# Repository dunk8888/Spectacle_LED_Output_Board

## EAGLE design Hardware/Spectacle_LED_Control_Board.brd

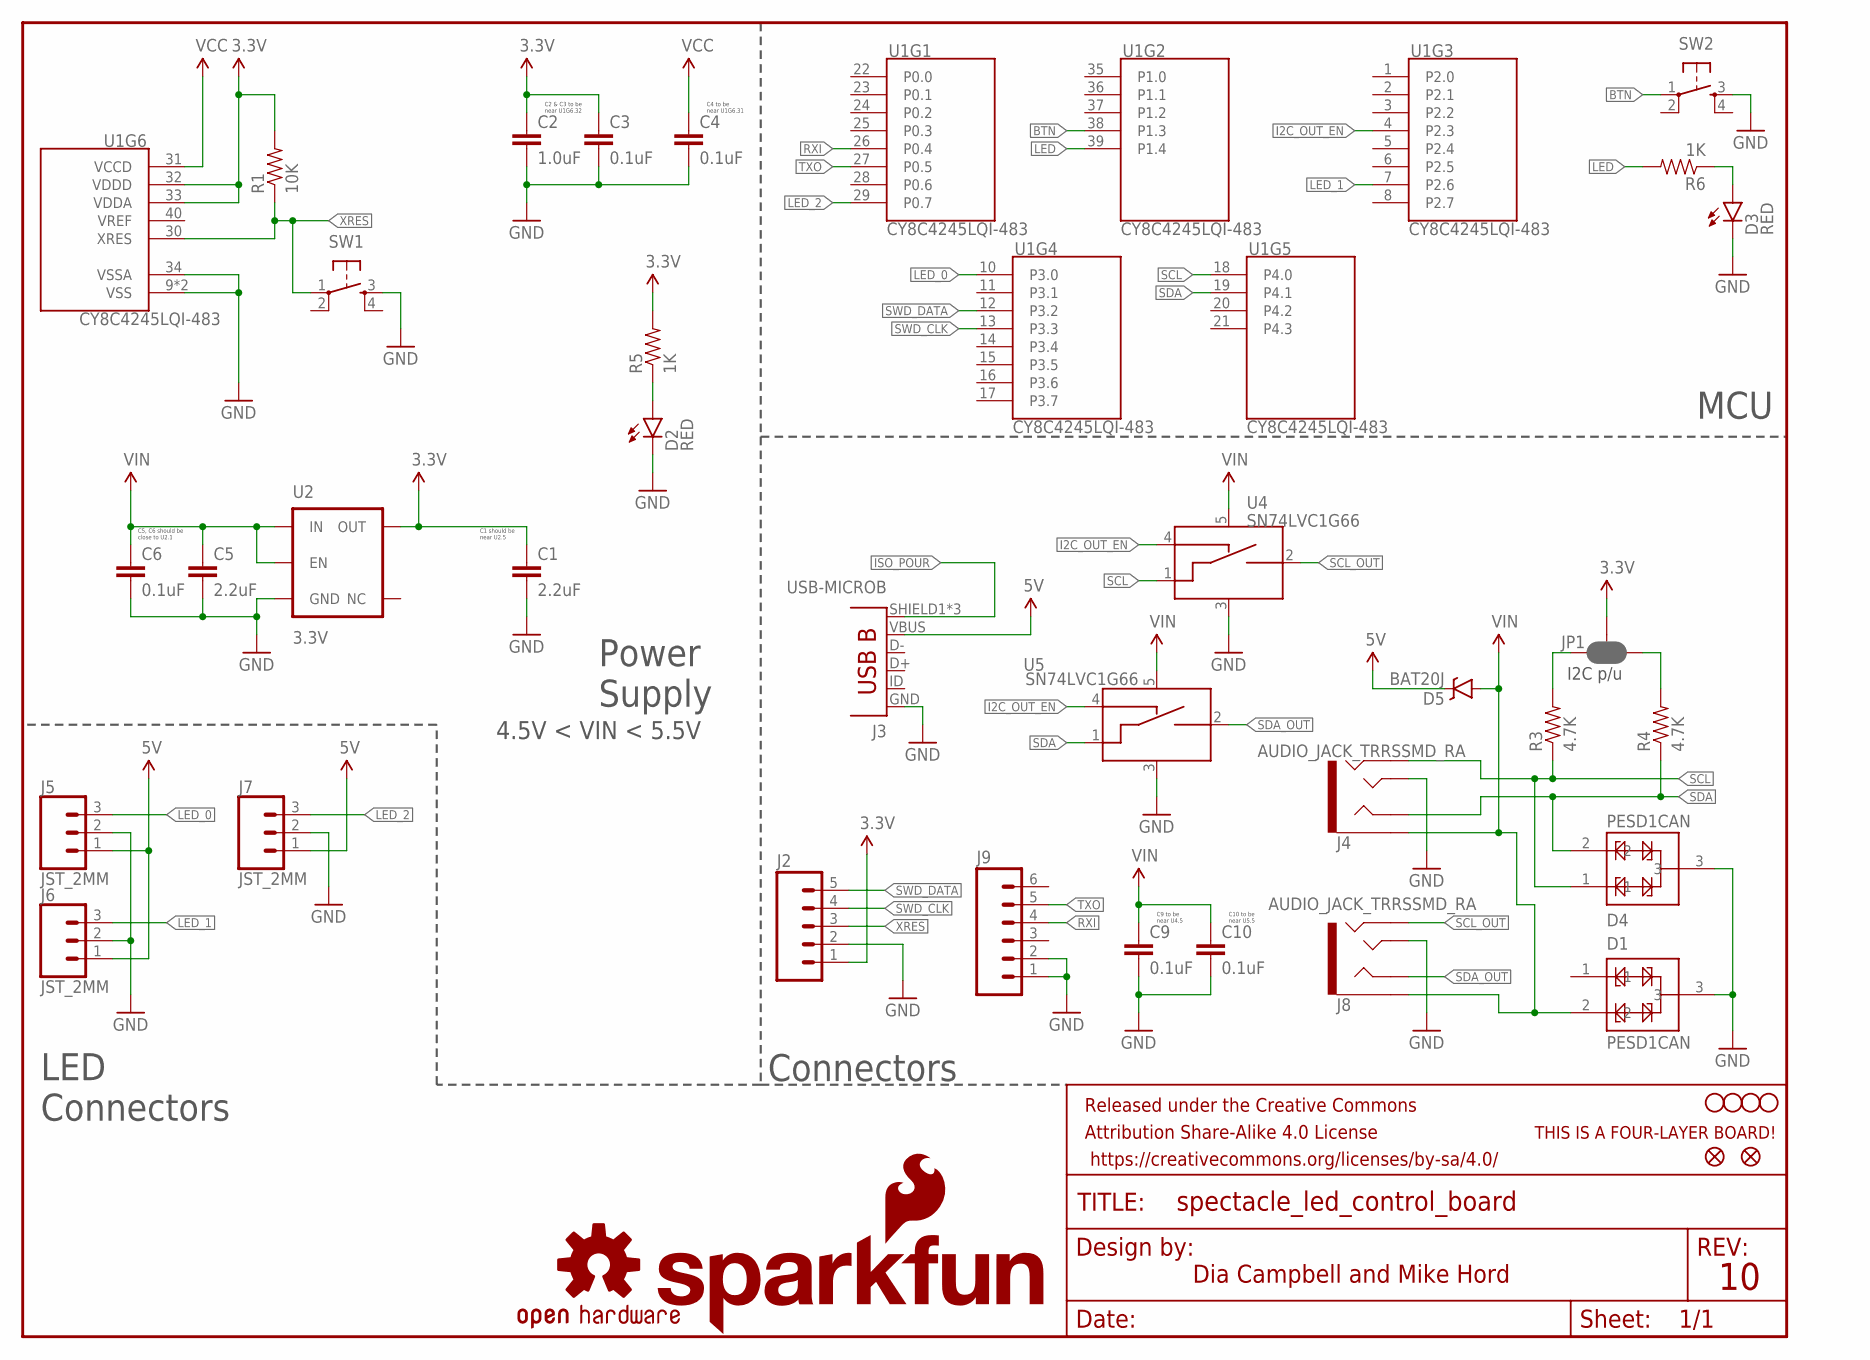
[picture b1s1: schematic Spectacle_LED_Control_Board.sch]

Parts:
C1, C5: 2.2uF; 0603-CAP
C2: 1.0uF; 0402-CAP
C3, C4, C6, C9, C10: 0.1uF; 0402-CAP
D1, D4: PESD1CAN; SOT23-3
D2, D3: RED; LED-0603
D5: BAT20J; SOD-323
FD1, FD2: FIDUCIALUFIDUCIAL; MICRO-FIDUCIAL
FRAME1: FRAME-LETTER; CREATIVE_COMMONS
H1, H2, H3, H4: STAND-OFF
J2: M05NO_SILK; 1X05_NO_SILK
J3: USB-MICROB; USB-B-MICRO-SMD_V03
J4, J8: AUDIO_JACK_TRRSSMD_RA; AUDIO_JACK_3.5MM_TRRS_SMD_RA
J5, J6, J7: JST_2MM; JST-3-PTH-VERT
J9: M06NO_SILK_NO_POP; 1X06_NO_SILK
JP1: JUMPER-PAD-3-NC_BY_PASTE; PAD-JUMPER-3-NC_BY_PASTE_YES_SILK_FULL_BOX
LOGO1: OSHW-LOGOS; OSHW-LOGO-S
LOGO2: SFE_LOGO_NAME_FLAME.1_INCH; SFE_LOGO_NAME_FLAME_.1
R1: 10K; 0603-RES
R3, R4: 4.7K; 0603-RES
R5, R6: 1K; 0603-RES
SW1, SW2: SWITCH_SPST_4_PINRECT; TACTILE_SWITCH_SMD_4.6X2.8MM
U1: CY8C4245LQI-483; QFN-40
U2: 3.3V; SOT23-5
U4, U5: SN74LVC1G66; SOT23-5
U$1: FOUR_LAYER_WARNING

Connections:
3.3V: C1.1, C2.1, C3.1, J2.1, JP1.2, R1.2, R5.2, U1.32 (VDDD), U1.33 (VDDA), U2.5 (OUT)
5V: D5.C, J3.VBUS, J5.1, J6.1, J7.1
BTN: SW2.1, U1.38 (P1.3)
GND: C1.2, C2.2, C3.2, C4.2, C5.2, C6.2, C9.2, C10.2, D1.3, D2.C, D3.C, D4.3, J2.2, J3.GND, J4.TIP, J5.2, J6.2, J7.2, J8.TIP, J9.1, J9.2, SW1.3, SW2.3, U1.9 (VSS), U1.34 (VSSA), U1.EP (VSS), U2.2 (GND), U4.3 (VSS), U5.3 (VSS)
I2C_OUT_EN: U1.4 (P2.3), U4.4 (CTRL_IN), U5.4 (CTRL_IN)
ISO_POUR: J3.SHIELD1 (SHIELD), J3.SHIELD2 (SHIELD), J3.SHIELD3 (SHIELD)
LED: R6.2, U1.39 (P1.4)
LED_0: J5.3, U1.10 (P3.0)
LED_1: J6.3, U1.7 (P2.6)
LED_2: J7.3, U1.29 (P0.7)
unnamed: JP1.3, R3.2
unnamed: D2.A, R5.1
unnamed: D3.A, R6.1
unnamed: JP1.1, R4.2
RXI: J9.4, U1.26 (P0.4)
SCL: D4.1, J4.RING2, R3.1, U1.18 (P4.0), U4.1 (A_IN)
SCL_OUT: J8.RING2, U4.2 (A_OUT)
SDA: D4.2, J4.RING1, R4.1, U1.19 (P4.1), U5.1 (A_IN)
SDA_OUT: J8.RING1, U5.2 (A_OUT)
SWD_CLK: J2.4, U1.13 (P3.3)
SWD_DATA: J2.5, U1.12 (P3.2)
TXO: J9.5, U1.27 (P0.5)
VCC: C4.1, U1.31 (VCCD)
VIN: C5.1, C6.1, C9.1, C10.1, D1.2, D5.A, J4.EARTH, J8.EARTH, U2.1 (IN), U2.3 (EN), U4.5 (VCC), U5.5 (VCC)
XRES: J2.3, R1.1, SW1.1, U1.30 (XRES)

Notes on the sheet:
C2 & C3 to be near U1G6.32
C4 to be near U1G6.31
Dia Campbell and Mike Hord
MCU
Connectors
LED Connectors
Power Supply
4.5V < VIN < 5.5V
I2C p/u
C9 to be near U4.5
C10 to be near U5.5
C5, C6 should be close to U2.1
C1 should be near U2.5

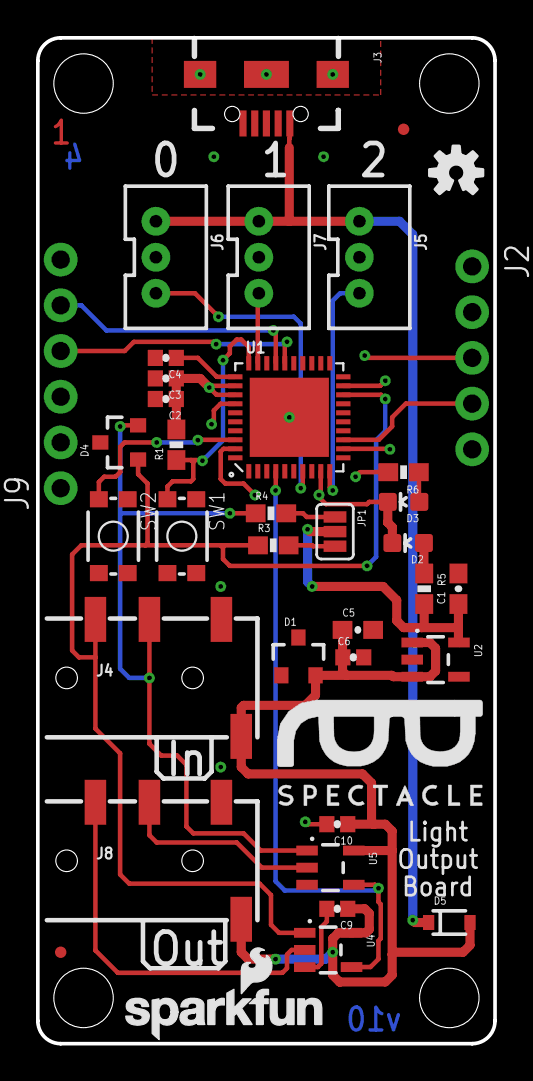
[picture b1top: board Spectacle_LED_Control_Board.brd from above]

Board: 4 copper layers, 25.4 x 55.9 mm, 44 parts (0 on the bottom side), 25 nets.

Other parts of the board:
U$2: ORDERING_INSTRUCTIONS

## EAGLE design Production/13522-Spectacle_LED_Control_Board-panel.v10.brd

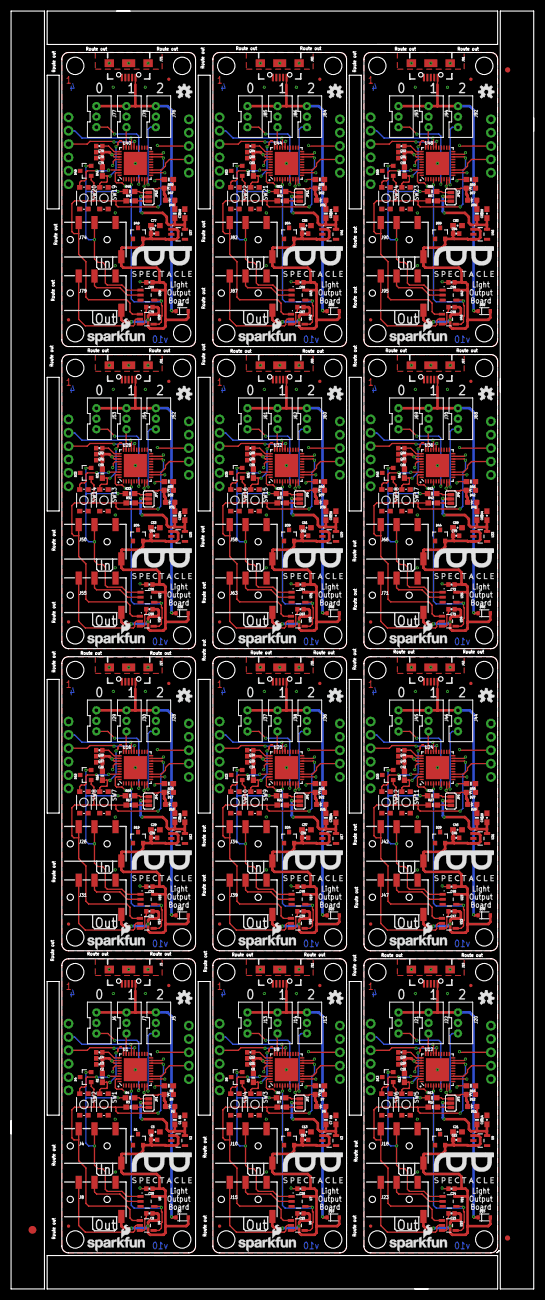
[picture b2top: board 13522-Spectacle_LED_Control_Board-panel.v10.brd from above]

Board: 4 copper layers, 99.3 x 242.8 mm, 495 parts (0 on the bottom side), 300 nets.

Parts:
C1, C5, C7, C13, C17, C21, C25, C29, C33, C37, C41, C45, C49, C53, C57, C61, C65, C69, C73, C77, C81, C85, C89, C93: 2.2uF; 0603-CAP
C2, C8, C18, C26, C34, C42, C50, C58, C66, C74, C82, C90: 1.0uF; 0402-CAP
C3, C4, C6, C9, C10, C11, C12, C14, C15, C16, C19, C20, C22, C23, C24, C27, C28, C30, C31, C32, C35, C36, C38, C39, C40, C43, C44, C46, C47, C48, C51, C52, C54, C55, C56, C59, C60, C62, C63, C64, C67, C68, C70, C71, C72, C75, C76, C78, C79, C80, C83, C84, C86, C87, C88, C91, C92, C94, C95, C96: 0.1uF; 0402-CAP
D1, D4, D8, D9, D13, D14, D18, D19, D23, D24, D28, D29, D33, D34, D38, D39, D43, D44, D48, D49, D53, D54, D58, D59: PESD1CAN; SOT23-3
D2, D3, D6, D7, D11, D12, D16, D17, D21, D22, D26, D27, D31, D32, D36, D37, D41, D42, D46, D47, D51, D52, D56, D57: RED; LED-0603
D5, D10, D15, D20, D25, D30, D35, D40, D45, D50, D55, D60: BAT20J; SOD-323
E$1: FIDUCIAL-1.5X3
E$4, E$7: FIDUCIAL-1X2
FD1, FD2, FD3, FD4, FD5, FD6, FD7, FD8, FD9, FD10, FD11, FD12, FD13, FD14, FD15, FD16, FD17, FD18, FD19, FD20, FD21, FD22, FD23, FD24: FIDUCIALUFIDUCIAL; MICRO-FIDUCIAL
H1, H2, H3, H4, H5, H6, H7, H8, H9, H10, H11, H12, H13, H14, H15, H16, H17, H18, H19, H20, H21, H22, H23, H24, H25, H26, H27, H28, H29, H30, H31, H32, H33, H34, H35, H36, H37, H38, H39, H40, H41, H42, H43, H44, H45, H46, H47, H48: STAND-OFF
J1, J2, J17, J25, J33, J41, J49, J57, J65, J73, J81, J89: 1X05_NO_SILK
J3, J11, J19, J27, J35, J43, J51, J59, J67, J75, J83, J91: USB-MICROB; USB-B-MICRO-SMD_V03
J4, J8, J10, J15, J18, J23, J26, J31, J34, J39, J42, J47, J50, J55, J58, J63, J66, J71, J74, J79, J82, J87, J90, J95: AUDIO_JACK_TRRSSMD_RA; AUDIO_JACK_3.5MM_TRRS_SMD_RA
J5, J6, J7, J12, J13, J14, J20, J21, J22, J28, J29, J30, J36, J37, J38, J44, J45, J46, J52, J53, J54, J60, J61, J62, J68, J69, J70, J76, J77, J78, J84, J85, J86, J92, J93, J94: JST_2MM; JST-3-PTH-VERT
J9, J16, J24, J32, J40, J48, J56, J64, J72, J80, J88, J96: 1X06_NO_SILK
JP1, JP2, JP3, JP4, JP5, JP6, JP7, JP8, JP9, JP10, JP11, JP12: JUMPER-PAD-3-NC_BY_PASTE; PAD-JUMPER-3-NC_BY_PASTE_YES_SILK_FULL_BOX
LOGO1, LOGO3, LOGO5, LOGO7, LOGO9, LOGO11, LOGO13, LOGO15, LOGO17, LOGO19, LOGO21, LOGO23: OSHW-LOGOS; OSHW-LOGO-S
LOGO2, LOGO4, LOGO6, LOGO8, LOGO10, LOGO12, LOGO14, LOGO16, LOGO18, LOGO20, LOGO22, LOGO24: SFE_LOGO_NAME_FLAME.1_INCH; SFE_LOGO_NAME_FLAME_.1
R1, R2, R11, R16, R21, R26, R31, R36, R41, R46, R51, R56: 10K; 0603-RES
R3, R4, R7, R8, R12, R13, R17, R18, R22, R23, R27, R28, R32, R33, R37, R38, R42, R43, R47, R48, R52, R53, R57, R58: 4.7K; 0603-RES
R5, R6, R9, R10, R14, R15, R19, R20, R24, R25, R29, R30, R34, R35, R39, R40, R44, R45, R49, R50, R54, R55, R59, R60: 1K; 0603-RES
SW1, SW2, SW3, SW4, SW5, SW6, SW7, SW8, SW9, SW10, SW11, SW12, SW13, SW14, SW15, SW16, SW17, SW18, SW19, SW20, SW21, SW22, SW23, SW24: TACTILE_SWITCH_SMD_4.6X2.8MM
U1, U8, U12, U16, U20, U24, U28, U32, U36, U40, U44, U48: CY8C4245LQI-483; QFN-40
U2, U3, U9, U13, U17, U21, U25, U29, U33, U37, U41, U45: 3.3V; SOT23-5
U4, U5, U6, U7, U10, U11, U14, U15, U18, U19, U22, U23, U26, U27, U30, U31, U34, U35, U38, U39, U42, U43, U46, U47: SN74LVC1G66; SOT23-5

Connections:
3.3V: C1.1, C2.1, C3.1, J2.1, JP1.2, R1.2, R5.2, U1.32, U1.33, U2.5
3.3V1: C7.1, C8.1, C11.1, J1.1, JP2.2, R2.2, R9.2, U3.5, U8.32, U8.33
3.3V2: C17.1, C18.1, C19.1, J17.1, JP3.2, R11.2, R14.2, U9.5, U12.32, U12.33
3.3V3: C25.1, C26.1, C27.1, J25.1, JP4.2, R16.2, R19.2, U13.5, U16.32, U16.33
3.3V4: C33.1, C34.1, C35.1, J33.1, JP5.2, R21.2, R24.2, U17.5, U20.32, U20.33
3.3V5: C41.1, C42.1, C43.1, J41.1, JP6.2, R26.2, R29.2, U21.5, U24.32, U24.33
3.3V6: C49.1, C50.1, C51.1, J49.1, JP7.2, R31.2, R34.2, U25.5, U28.32, U28.33
3.3V7: C57.1, C58.1, C59.1, J57.1, JP8.2, R36.2, R39.2, U29.5, U32.32, U32.33
3.3V8: C65.1, C66.1, C67.1, J65.1, JP9.2, R41.2, R44.2, U33.5, U36.32, U36.33
3.3V9: C73.1, C74.1, C75.1, J73.1, JP10.2, R46.2, R49.2, U37.5, U40.32, U40.33
3.3V10: C81.1, C82.1, C83.1, J81.1, JP11.2, R51.2, R54.2, U41.5, U44.32, U44.33
3.3V11: C89.1, C90.1, C91.1, J89.1, JP12.2, R56.2, R59.2, U45.5, U48.32, U48.33
5V: D5.C, J3.VBUS, J5.1, J6.1, J7.1
5V1: D10.C, J11.VBUS, J12.1, J13.1, J14.1
5V2: D15.C, J19.VBUS, J20.1, J21.1, J22.1
5V3: D20.C, J27.VBUS, J28.1, J29.1, J30.1
5V4: D25.C, J35.VBUS, J36.1, J37.1, J38.1
5V5: D30.C, J43.VBUS, J44.1, J45.1, J46.1
5V6: D35.C, J51.VBUS, J52.1, J53.1, J54.1
5V7: D40.C, J59.VBUS, J60.1, J61.1, J62.1
5V8: D45.C, J67.VBUS, J68.1, J69.1, J70.1
5V9: D50.C, J75.VBUS, J76.1, J77.1, J78.1
5V10: D55.C, J83.VBUS, J84.1, J85.1, J86.1
5V11: D60.C, J91.VBUS, J92.1, J93.1, J94.1
BTN: SW2.1, U1.38
BTN1: SW4.1, U8.38
BTN2: SW6.1, U12.38
BTN3: SW8.1, U16.38
BTN4: SW10.1, U20.38
BTN5: SW12.1, U24.38
BTN6: SW14.1, U28.38
BTN7: SW16.1, U32.38
BTN8: SW18.1, U36.38
BTN9: SW20.1, U40.38
BTN10: SW22.1, U44.38
BTN11: SW24.1, U48.38
GND: C1.2, C2.2, C3.2, C4.2, C5.2, C6.2, C9.2, C10.2, D1.3, D2.C, D3.C, D4.3, J2.2, J3.GND, J4.TIP, J5.2, J6.2, J7.2, J8.TIP, J9.1, J9.2, SW1.3, SW2.3, U1.9, U1.34, U1.EP, U2.2, U4.3, U5.3
GND1: C7.2, C8.2, C11.2, C12.2, C13.2, C14.2, C15.2, C16.2, D6.C, D7.C, D8.3, D9.3, J1.2, J10.TIP, J11.GND, J12.2, J13.2, J14.2, J15.TIP, J16.1, J16.2, SW3.3, SW4.3, U3.2, U6.3, U7.3, U8.9, U8.34, U8.EP
GND2: C17.2, C18.2, C19.2, C20.2, C21.2, C22.2, C23.2, C24.2, D11.C, D12.C, D13.3, D14.3, J17.2, J18.TIP, J19.GND, J20.2, J21.2, J22.2, J23.TIP, J24.1, J24.2, SW5.3, SW6.3, U9.2, U10.3, U11.3, U12.9, U12.34, U12.EP
GND3: C25.2, C26.2, C27.2, C28.2, C29.2, C30.2, C31.2, C32.2, D16.C, D17.C, D18.3, D19.3, J25.2, J26.TIP, J27.GND, J28.2, J29.2, J30.2, J31.TIP, J32.1, J32.2, SW7.3, SW8.3, U13.2, U14.3, U15.3, U16.9, U16.34, U16.EP
GND4: C33.2, C34.2, C35.2, C36.2, C37.2, C38.2, C39.2, C40.2, D21.C, D22.C, D23.3, D24.3, J33.2, J34.TIP, J35.GND, J36.2, J37.2, J38.2, J39.TIP, J40.1, J40.2, SW9.3, SW10.3, U17.2, U18.3, U19.3, U20.9, U20.34, U20.EP
GND5: C41.2, C42.2, C43.2, C44.2, C45.2, C46.2, C47.2, C48.2, D26.C, D27.C, D28.3, D29.3, J41.2, J42.TIP, J43.GND, J44.2, J45.2, J46.2, J47.TIP, J48.1, J48.2, SW11.3, SW12.3, U21.2, U22.3, U23.3, U24.9, U24.34, U24.EP
GND6: C49.2, C50.2, C51.2, C52.2, C53.2, C54.2, C55.2, C56.2, D31.C, D32.C, D33.3, D34.3, J49.2, J50.TIP, J51.GND, J52.2, J53.2, J54.2, J55.TIP, J56.1, J56.2, SW13.3, SW14.3, U25.2, U26.3, U27.3, U28.9, U28.34, U28.EP
GND7: C57.2, C58.2, C59.2, C60.2, C61.2, C62.2, C63.2, C64.2, D36.C, D37.C, D38.3, D39.3, J57.2, J58.TIP, J59.GND, J60.2, J61.2, J62.2, J63.TIP, J64.1, J64.2, SW15.3, SW16.3, U29.2, U30.3, U31.3, U32.9, U32.34, U32.EP
GND8: C65.2, C66.2, C67.2, C68.2, C69.2, C70.2, C71.2, C72.2, D41.C, D42.C, D43.3, D44.3, J65.2, J66.TIP, J67.GND, J68.2, J69.2, J70.2, J71.TIP, J72.1, J72.2, SW17.3, SW18.3, U33.2, U34.3, U35.3, U36.9, U36.34, U36.EP
GND9: C73.2, C74.2, C75.2, C76.2, C77.2, C78.2, C79.2, C80.2, D46.C, D47.C, D48.3, D49.3, J73.2, J74.TIP, J75.GND, J76.2, J77.2, J78.2, J79.TIP, J80.1, J80.2, SW19.3, SW20.3, U37.2, U38.3, U39.3, U40.9, U40.34, U40.EP
GND10: C81.2, C82.2, C83.2, C84.2, C85.2, C86.2, C87.2, C88.2, D51.C, D52.C, D53.3, D54.3, J81.2, J82.TIP, J83.GND, J84.2, J85.2, J86.2, J87.TIP, J88.1, J88.2, SW21.3, SW22.3, U41.2, U42.3, U43.3, U44.9, U44.34, U44.EP
GND11: C89.2, C90.2, C91.2, C92.2, C93.2, C94.2, C95.2, C96.2, D56.C, D57.C, D58.3, D59.3, J89.2, J90.TIP, J91.GND, J92.2, J93.2, J94.2, J95.TIP, J96.1, J96.2, SW23.3, SW24.3, U45.2, U46.3, U47.3, U48.9, U48.34, U48.EP
I2C_OUT_EN: U1.4, U4.4, U5.4
I2C_OUT_EN1: U6.4, U7.4, U8.4
I2C_OUT_EN2: U10.4, U11.4, U12.4
I2C_OUT_EN3: U14.4, U15.4, U16.4
I2C_OUT_EN4: U18.4, U19.4, U20.4
I2C_OUT_EN5: U22.4, U23.4, U24.4
I2C_OUT_EN6: U26.4, U27.4, U28.4
I2C_OUT_EN7: U30.4, U31.4, U32.4
I2C_OUT_EN8: U34.4, U35.4, U36.4
I2C_OUT_EN9: U38.4, U39.4, U40.4
I2C_OUT_EN10: U42.4, U43.4, U44.4
I2C_OUT_EN11: U46.4, U47.4, U48.4
ISO_POUR: J3.SHIELD1, J3.SHIELD2, J3.SHIELD3
ISO_POUR1: J11.SHIELD1, J11.SHIELD2, J11.SHIELD3
ISO_POUR2: J19.SHIELD1, J19.SHIELD2, J19.SHIELD3
ISO_POUR3: J27.SHIELD1, J27.SHIELD2, J27.SHIELD3
ISO_POUR4: J35.SHIELD1, J35.SHIELD2, J35.SHIELD3
ISO_POUR5: J43.SHIELD1, J43.SHIELD2, J43.SHIELD3
ISO_POUR6: J51.SHIELD1, J51.SHIELD2, J51.SHIELD3
ISO_POUR7: J59.SHIELD1, J59.SHIELD2, J59.SHIELD3
ISO_POUR8: J67.SHIELD1, J67.SHIELD2, J67.SHIELD3
ISO_POUR9: J75.SHIELD1, J75.SHIELD2, J75.SHIELD3
ISO_POUR10: J83.SHIELD1, J83.SHIELD2, J83.SHIELD3
ISO_POUR11: J91.SHIELD1, J91.SHIELD2, J91.SHIELD3
LED: R6.2, U1.39
LED1: R10.2, U8.39
LED2: R15.2, U12.39
LED3: R20.2, U16.39
LED4: R25.2, U20.39
LED5: R30.2, U24.39
LED6: R35.2, U28.39
LED7: R40.2, U32.39
LED8: R45.2, U36.39
LED9: R50.2, U40.39
LED10: R55.2, U44.39
LED11: R60.2, U48.39
LED_0: J5.3, U1.10
LED_1: J6.3, U1.7
LED_2: J7.3, U1.29
LED_3: J12.3, U8.10
LED_4: J13.3, U8.7
LED_5: J14.3, U8.29
LED_6: J20.3, U12.10
LED_7: J21.3, U12.7
LED_8: J22.3, U12.29
LED_9: J28.3, U16.10
LED_10: J29.3, U16.7
LED_11: J30.3, U16.29
LED_12: J36.3, U20.10
LED_13: J37.3, U20.7
LED_14: J38.3, U20.29
LED_15: J44.3, U24.10
LED_16: J45.3, U24.7
LED_17: J46.3, U24.29
LED_18: J52.3, U28.10
LED_19: J53.3, U28.7
LED_20: J54.3, U28.29
LED_21: J60.3, U32.10
LED_22: J61.3, U32.7
LED_23: J62.3, U32.29
LED_24: J68.3, U36.10
LED_25: J69.3, U36.7
LED_26: J70.3, U36.29
LED_27: J76.3, U40.10
LED_28: J77.3, U40.7
LED_29: J78.3, U40.29
LED_30: J84.3, U44.10
LED_31: J85.3, U44.7
LED_32: J86.3, U44.29
LED_33: J92.3, U48.10
LED_34: J93.3, U48.7
LED_35: J94.3, U48.29
unnamed: JP2.3, R7.2
unnamed: JP1.3, R3.2
unnamed: JP2.1, R8.2
unnamed: D2.A, R5.1
unnamed: D3.A, R6.1
unnamed: JP1.1, R4.2
unnamed: D6.A, R9.1
unnamed: D7.A, R10.1
unnamed: JP3.3, R12.2
unnamed: JP3.1, R13.2
unnamed: D11.A, R14.1
unnamed: D12.A, R15.1
unnamed: JP4.3, R17.2
unnamed: JP4.1, R18.2
unnamed: D16.A, R19.1
unnamed: D17.A, R20.1
unnamed: JP5.3, R22.2
unnamed: JP5.1, R23.2
unnamed: D21.A, R24.1
unnamed: D22.A, R25.1
unnamed: JP6.3, R27.2
unnamed: JP6.1, R28.2
unnamed: D26.A, R29.1
unnamed: D27.A, R30.1
unnamed: JP7.3, R32.2
unnamed: JP7.1, R33.2
unnamed: D31.A, R34.1
unnamed: D32.A, R35.1
unnamed: JP8.3, R37.2
unnamed: JP8.1, R38.2
unnamed: D36.A, R39.1
unnamed: D37.A, R40.1
unnamed: JP9.3, R42.2
unnamed: JP9.1, R43.2
unnamed: D41.A, R44.1
unnamed: D42.A, R45.1
unnamed: JP10.3, R47.2
unnamed: JP10.1, R48.2
unnamed: D46.A, R49.1
unnamed: D47.A, R50.1
unnamed: JP11.3, R52.2
unnamed: JP11.1, R53.2
unnamed: D51.A, R54.1
unnamed: D52.A, R55.1
unnamed: JP12.3, R57.2
unnamed: JP12.1, R58.2
unnamed: D56.A, R59.1
unnamed: D57.A, R60.1
RXI: J9.4, U1.26
RXI1: J16.4, U8.26
RXI2: J24.4, U12.26
RXI3: J32.4, U16.26
RXI4: J40.4, U20.26
RXI5: J48.4, U24.26
RXI6: J56.4, U28.26
RXI7: J64.4, U32.26
RXI8: J72.4, U36.26
RXI9: J80.4, U40.26
RXI10: J88.4, U44.26
RXI11: J96.4, U48.26
SCL: D4.1, J4.RING2, R3.1, U1.18, U4.1
SCL1: D8.1, J10.RING2, R7.1, U6.1, U8.18
SCL2: D13.1, J18.RING2, R12.1, U10.1, U12.18
SCL3: D18.1, J26.RING2, R17.1, U14.1, U16.18
SCL4: D23.1, J34.RING2, R22.1, U18.1, U20.18
SCL5: D28.1, J42.RING2, R27.1, U22.1, U24.18
SCL6: D33.1, J50.RING2, R32.1, U26.1, U28.18
SCL7: D38.1, J58.RING2, R37.1, U30.1, U32.18
SCL8: D43.1, J66.RING2, R42.1, U34.1, U36.18
SCL9: D48.1, J74.RING2, R47.1, U38.1, U40.18
SCL10: D53.1, J82.RING2, R52.1, U42.1, U44.18
SCL11: D58.1, J90.RING2, R57.1, U46.1, U48.18
SCL_OUT: J8.RING2, U4.2
SCL_OUT1: J15.RING2, U6.2
SCL_OUT2: J23.RING2, U10.2
SCL_OUT3: J31.RING2, U14.2
SCL_OUT4: J39.RING2, U18.2
SCL_OUT5: J47.RING2, U22.2
SCL_OUT6: J55.RING2, U26.2
SCL_OUT7: J63.RING2, U30.2
SCL_OUT8: J71.RING2, U34.2
SCL_OUT9: J79.RING2, U38.2
SCL_OUT10: J87.RING2, U42.2
SCL_OUT11: J95.RING2, U46.2
SDA: D4.2, J4.RING1, R4.1, U1.19, U5.1
SDA1: D8.2, J10.RING1, R8.1, U7.1, U8.19
SDA2: D13.2, J18.RING1, R13.1, U11.1, U12.19
SDA3: D18.2, J26.RING1, R18.1, U15.1, U16.19
SDA4: D23.2, J34.RING1, R23.1, U19.1, U20.19
SDA5: D28.2, J42.RING1, R28.1, U23.1, U24.19
SDA6: D33.2, J50.RING1, R33.1, U27.1, U28.19
SDA7: D38.2, J58.RING1, R38.1, U31.1, U32.19
SDA8: D43.2, J66.RING1, R43.1, U35.1, U36.19
SDA9: D48.2, J74.RING1, R48.1, U39.1, U40.19
SDA10: D53.2, J82.RING1, R53.1, U43.1, U44.19
SDA11: D58.2, J90.RING1, R58.1, U47.1, U48.19
SDA_OUT: J8.RING1, U5.2
SDA_OUT1: J15.RING1, U7.2
SDA_OUT2: J23.RING1, U11.2
SDA_OUT3: J31.RING1, U15.2
SDA_OUT4: J39.RING1, U19.2
SDA_OUT5: J47.RING1, U23.2
SDA_OUT6: J55.RING1, U27.2
SDA_OUT7: J63.RING1, U31.2
SDA_OUT8: J71.RING1, U35.2
SDA_OUT9: J79.RING1, U39.2
SDA_OUT10: J87.RING1, U43.2
SDA_OUT11: J95.RING1, U47.2
SWD_CLK: J2.4, U1.13
SWD_CLK1: J1.4, U8.13
SWD_CLK2: J17.4, U12.13
SWD_CLK3: J25.4, U16.13
SWD_CLK4: J33.4, U20.13
SWD_CLK5: J41.4, U24.13
SWD_CLK6: J49.4, U28.13
SWD_CLK7: J57.4, U32.13
SWD_CLK8: J65.4, U36.13
SWD_CLK9: J73.4, U40.13
SWD_CLK10: J81.4, U44.13
SWD_CLK11: J89.4, U48.13
SWD_DATA: J2.5, U1.12
SWD_DATA1: J1.5, U8.12
SWD_DATA2: J17.5, U12.12
SWD_DATA3: J25.5, U16.12
SWD_DATA4: J33.5, U20.12
SWD_DATA5: J41.5, U24.12
SWD_DATA6: J49.5, U28.12
SWD_DATA7: J57.5, U32.12
SWD_DATA8: J65.5, U36.12
SWD_DATA9: J73.5, U40.12
SWD_DATA10: J81.5, U44.12
SWD_DATA11: J89.5, U48.12
TXO: J9.5, U1.27
TXO1: J16.5, U8.27
TXO2: J24.5, U12.27
TXO3: J32.5, U16.27
TXO4: J40.5, U20.27
TXO5: J48.5, U24.27
TXO6: J56.5, U28.27
TXO7: J64.5, U32.27
TXO8: J72.5, U36.27
TXO9: J80.5, U40.27
TXO10: J88.5, U44.27
TXO11: J96.5, U48.27
VCC: C4.1, U1.31
VCC1: C12.1, U8.31
VCC2: C20.1, U12.31
VCC3: C28.1, U16.31
VCC4: C36.1, U20.31
VCC5: C44.1, U24.31
VCC6: C52.1, U28.31
VCC7: C60.1, U32.31
VCC8: C68.1, U36.31
VCC9: C76.1, U40.31
VCC10: C84.1, U44.31
VCC11: C92.1, U48.31
VIN: C5.1, C6.1, C9.1, C10.1, D1.2, D5.A, J4.EARTH, J8.EARTH, U2.1, U2.3, U4.5, U5.5
VIN1: C13.1, C14.1, C15.1, C16.1, D9.2, D10.A, J10.EARTH, J15.EARTH, U3.1, U3.3, U6.5, U7.5
VIN2: C21.1, C22.1, C23.1, C24.1, D14.2, D15.A, J18.EARTH, J23.EARTH, U9.1, U9.3, U10.5, U11.5
VIN3: C29.1, C30.1, C31.1, C32.1, D19.2, D20.A, J26.EARTH, J31.EARTH, U13.1, U13.3, U14.5, U15.5
VIN4: C37.1, C38.1, C39.1, C40.1, D24.2, D25.A, J34.EARTH, J39.EARTH, U17.1, U17.3, U18.5, U19.5
VIN5: C45.1, C46.1, C47.1, C48.1, D29.2, D30.A, J42.EARTH, J47.EARTH, U21.1, U21.3, U22.5, U23.5
VIN6: C53.1, C54.1, C55.1, C56.1, D34.2, D35.A, J50.EARTH, J55.EARTH, U25.1, U25.3, U26.5, U27.5
VIN7: C61.1, C62.1, C63.1, C64.1, D39.2, D40.A, J58.EARTH, J63.EARTH, U29.1, U29.3, U30.5, U31.5
VIN8: C69.1, C70.1, C71.1, C72.1, D44.2, D45.A, J66.EARTH, J71.EARTH, U33.1, U33.3, U34.5, U35.5
VIN9: C77.1, C78.1, C79.1, C80.1, D49.2, D50.A, J74.EARTH, J79.EARTH, U37.1, U37.3, U38.5, U39.5
VIN10: C85.1, C86.1, C87.1, C88.1, D54.2, D55.A, J82.EARTH, J87.EARTH, U41.1, U41.3, U42.5, U43.5
VIN11: C93.1, C94.1, C95.1, C96.1, D59.2, D60.A, J90.EARTH, J95.EARTH, U45.1, U45.3, U46.5, U47.5
XRES: J2.3, R1.1, SW1.1, U1.30
XRES1: J1.3, R2.1, SW3.1, U8.30
XRES2: J17.3, R11.1, SW5.1, U12.30
XRES3: J25.3, R16.1, SW7.1, U16.30
XRES4: J33.3, R21.1, SW9.1, U20.30
XRES5: J41.3, R26.1, SW11.1, U24.30
XRES6: J49.3, R31.1, SW13.1, U28.30
XRES7: J57.3, R36.1, SW15.1, U32.30
XRES8: J65.3, R41.1, SW17.1, U36.30
XRES9: J73.3, R46.1, SW19.1, U40.30
XRES10: J81.3, R51.1, SW21.1, U44.30
XRES11: J89.3, R56.1, SW23.1, U48.30

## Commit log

2016-07-15 Derived from servo board
2016-09-15 First layout draft
2016-09-15 Add spectacle logo silk
2016-09-20 review edit list
2016-09-20 Reduce paste apertures on QFN to 75%
2016-09-21 partial checklist fixes
2016-09-22 Review edits
2016-09-23 QC edits, round one
2016-09-23 checked isolates
2016-10-10 Working checkpoint for firmware
2016-10-10 Added circuitry for downstream power control
2016-10-10 Added enable pin
2016-10-13 Routed downstream power control
2016-10-13 airwire fix
2016-10-13 Added restrict and labled Vin and Vout connectors
2016-10-26 Added I2C switching hardware
2016-10-28 Power circuit revisions
2016-10-28 DRC fixes
2016-10-28 second round of DRC changes
2016-11-07 Changes from review
2016-11-07 File changes from checklist first pass
2016-11-08 Chg VREG to APK2112
2016-11-08 Fix VIN path per review
2016-11-08 Change pullups to 4.7k
2016-12-07 Semi-working entry, last for 4146 Has troubles with communicating I2C at the same time as LEDs updated. Transitioning to 4245
2016-12-13 Primarily for changing to PSOC4245LQI-483 Interstitial commit for firmware
2016-12-20 Firmware commit All functionality passes initial testing and is implemented.
2016-12-22 routing redesign with new processor
2016-12-22 Routing!
2016-12-30 Routed and ready to check
2017-01-04 moving caps
2017-01-12 ready for review!
2017-01-17 QC changes
    Moved labels, tidied schematic
2017-01-25 Changes in preparation for release - Added header to all files - Deleted a couple of unused files
2017-01-25 Reduced config data size
2017-02-10 Improved fade algorithm
2017-02-21 Changes for release to v10
2017-02-21 V10 feedback from QC review
2017-02-23 panel

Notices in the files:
parts and their libraries:
SparkFun-Aesthetics: Licensing: Creative Commons ShareAlike 4.0 International - https://creativecommons.org/licenses/by-sa/4.0
SparkFun-Aesthetics: Released under the Creative Commons Attribution Share-Alike 4.0 License
SparkFun-Aesthetics: https://creativecommons.org/licenses/by-sa/4.0
